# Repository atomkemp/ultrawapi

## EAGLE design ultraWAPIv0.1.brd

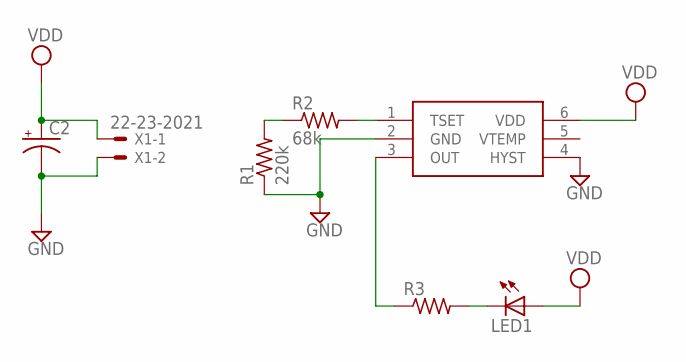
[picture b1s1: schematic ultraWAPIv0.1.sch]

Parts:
C2: CPOL-USE5-13; E5-13
LED1: LEDCHIP-LED0603; CHIP-LED0603
R1: 220k; R0603
R2: 68k; R0603
R3: R-US_R0603; R0603
U$1: TMP300B; TSOT23-6_DDC
X1: 22-23-2021

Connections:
GND: C2.-, R1.1, U$1.2 (GND), U$1.4 (HYST), X1.2
unnamed: LED1.C, R3.2
unnamed: R3.1, U$1.3 (OUT)
unnamed: R2.2, U$1.1 (TSET)
unnamed: R1.2, R2.1
VDD: C2.+, LED1.A, U$1.6 (VDD), X1.1

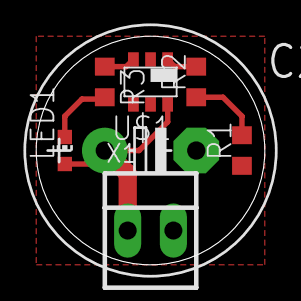
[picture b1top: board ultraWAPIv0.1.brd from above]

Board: 2 copper layers, 12.7 x 12.7 mm, 7 parts (0 on the bottom side), 6 nets.
